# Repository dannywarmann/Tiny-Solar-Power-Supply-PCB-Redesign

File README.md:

# Project Overview
This project is a learning-focused redesign of Elektor’s Tiny Solar Power Supply. The aim is to understand the fundamentals of solar energy harvesting and low-power power supply design through hands-on schematic capture and PCB layout.

The entire circuit and PCB were redesigned from scratch using KiCad EDA, while referring to the original Elektor concept strictly for educational and learning purposes

# Learning Objectives
- Understanding solar input conditioning and handling variable input sources
- Learning power regulation basics for low-power applications
- Developing component selection reasoning based on electrical and practical constraints
- Applying practical PCB layout considerations such as trace routing, grounding, and component placement

# Circuit Operation
The system starts with a solar panel as the primary energy source. Since solar output varies with light conditions, the input stage conditions and stabilizes this energy before it is used further.

The conditioned solar input is then passed to a DC-DC regulation stage, which converts the variable input voltage into a usable and stable output suitable for low-power electronic circuits. Passive components around the regulator help improve stability and efficiency.

Finally, the regulated output is made available through the output terminals, allowing it to power small loads or act as a learning reference for energy-harvesting power supplies.

# Images

|Schematic|Layout|
|---|---|
|  |  |

|Top|Bottom|
|---|---|
|  |  |

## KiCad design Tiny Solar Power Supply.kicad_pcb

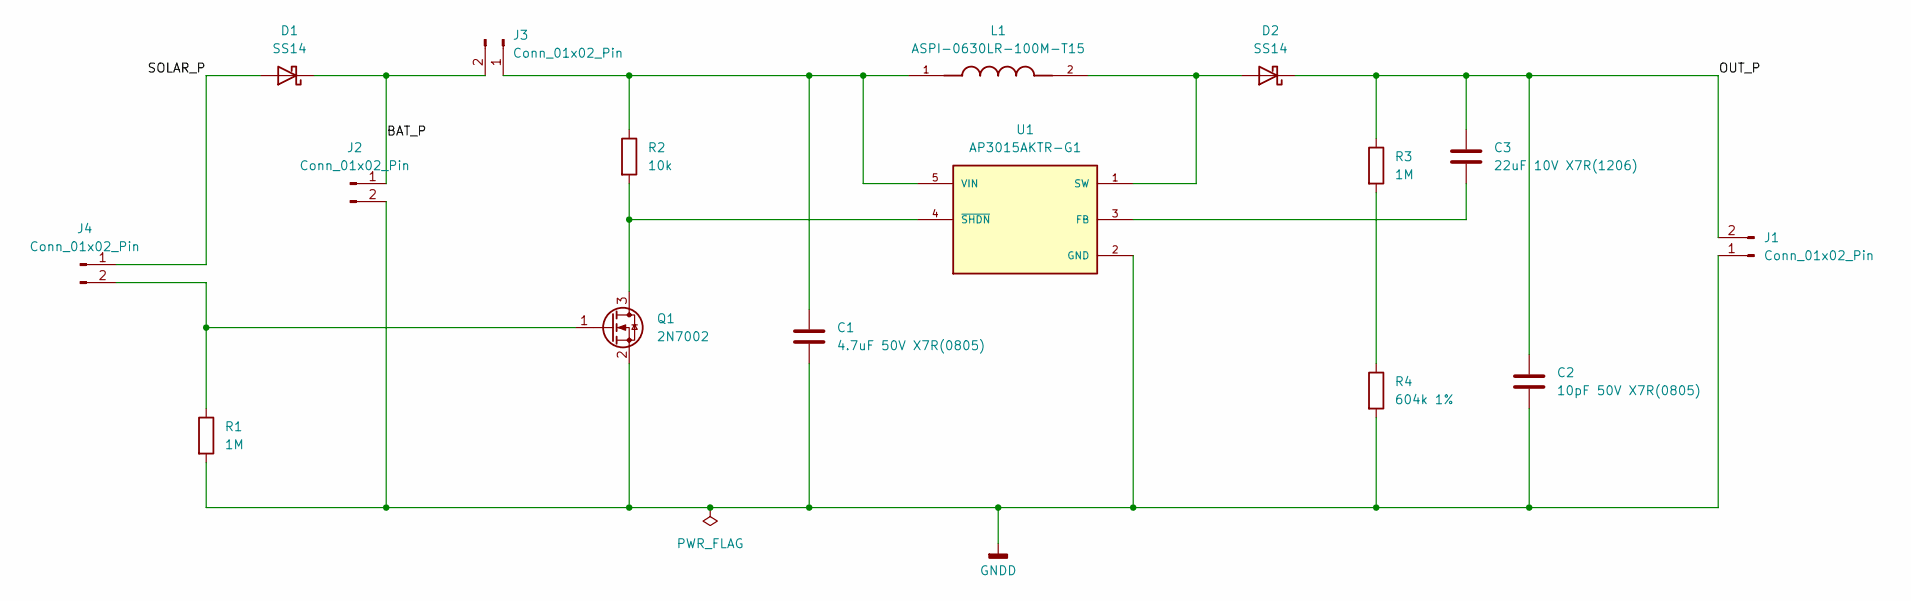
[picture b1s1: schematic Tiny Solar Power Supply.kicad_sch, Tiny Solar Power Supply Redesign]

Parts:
C1: 4.7uF 50V X7R(0805); C_0805_2012Metric
C2: 10pF 50V X7R(0805); C_0805_2012Metric
C3: 22uF 10V X7R(1206); C_1206_3216Metric
D1, D2: SS14; D_SMA
J1, J3, J4: Conn_01x02_Pin; PinHeader_1x02_P2.54mm_Horizontal
J2: Conn_01x02_Pin; SW_DIP_SPSTx01_Slide_9.78x4.72mm_W7.62mm_P2.54mm
L1: ASPI-0630LR-100M-T15; IND_ASPI-0630LR-100M-T15; PARTREV B
Q1: 2N7002; SOT-23
R1, R3: 1M; R_0805_2012Metric
R2: 10k; R_0805_2012Metric
R4: 604k 1%; R_0805_2012Metric
U1: AP3015AKTR-G1; SOT95P280X145-5N; PARTREV 1.4

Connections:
/BAT_P: D1.1 (K), J2.1, J3.2
/OUT_P: C2.1, C3.1, D2.1 (K), J1.2, R3.1
/SOLAR_P: D1.2 (A), J4.1
GNDD: C1.2, C2.2, J1.1, J2.2, Q1.2 (S), R1.2, R4.2, U1.2 (GND)
unnamed: D2.2 (A), L1.2, U1.1 (SW)
unnamed: C1.1, J3.1, L1.1, R2.1, U1.5 (VIN)
unnamed: J4.2, Q1.1 (G), R1.1
unnamed: Q1.3 (D), R2.2, U1.4 (~SHDN)
unnamed: R3.2, R4.1
unnamed: C3.2, U1.3 (FB)

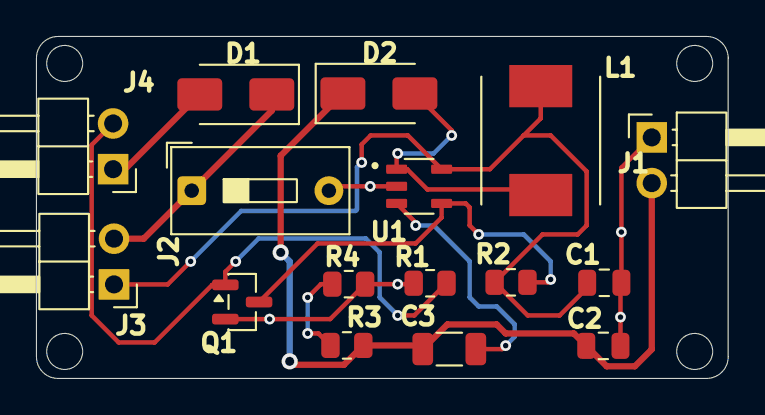
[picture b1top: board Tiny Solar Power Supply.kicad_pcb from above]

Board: 2 copper layers, 38.4 x 19.0 mm, 16 parts (0 on the bottom side), 10 nets.
